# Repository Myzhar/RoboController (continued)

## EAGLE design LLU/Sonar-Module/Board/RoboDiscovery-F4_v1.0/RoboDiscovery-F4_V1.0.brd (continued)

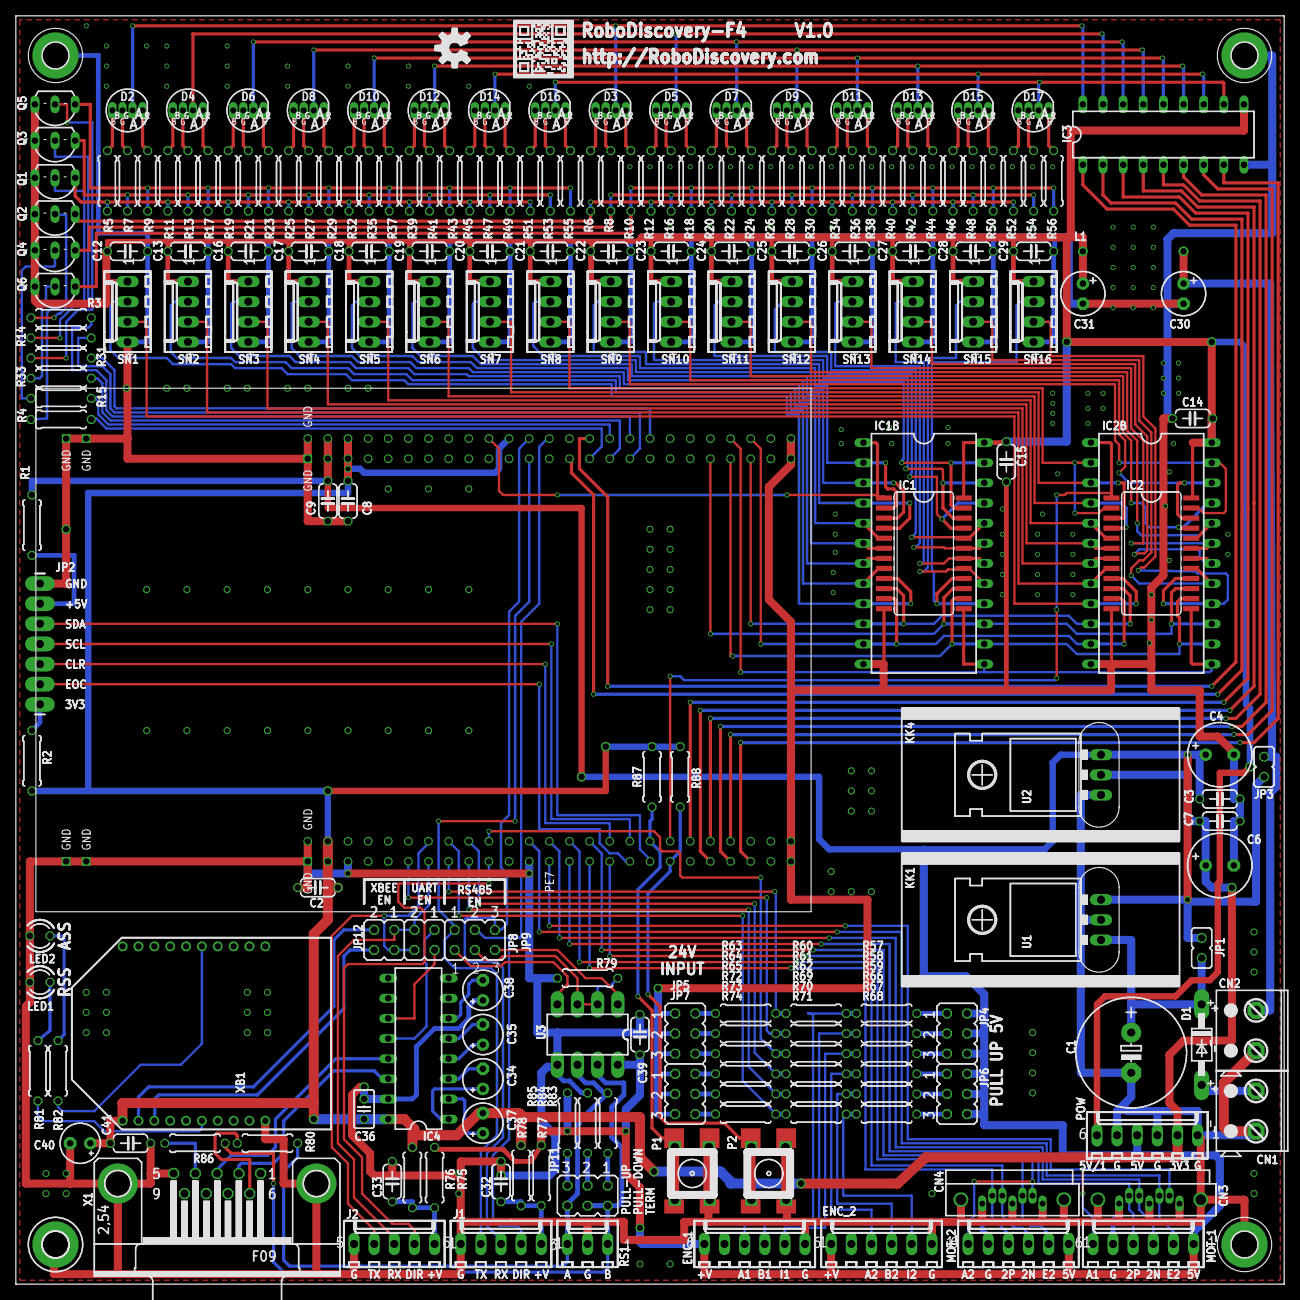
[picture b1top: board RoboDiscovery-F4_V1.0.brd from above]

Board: 2 copper layers, 160.0 x 160.0 mm, 212 parts (0 on the bottom side), 202 nets.

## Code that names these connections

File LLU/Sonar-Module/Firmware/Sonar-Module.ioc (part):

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Mcu.Name=STM32F407V(E-G)Tx
Mcu.Package=LQFP100
Mcu.UserName=STM32F407VGTx
PA0-WKUP.GPIOParameters=GPIO_Label,GPIO_PuPd,GPIO_Mode
PA0-WKUP.GPIO_Label=USER_BUT
PA0-WKUP.GPIO_Mode=GPIO_MODE_INPUT
PA0-WKUP.GPIO_PuPd=GPIO_NOPULL
PA0-WKUP.Signal=GPIO_Input
PA1.GPIOParameters=GPIO_Label,GPIO_Speed,GPIO_ModeDefaultPP,GPIO_PuPd
PA1.GPIO_Label=ENC1_B
PA1.GPIO_ModeDefaultPP=GPIO_MODE_AF_PP
PA1.GPIO_PuPd=GPIO_NOPULL
PA1.GPIO_Speed=GPIO_SPEED_LOW
PA1.Signal=S_TIM2_CH2
PA10.GPIOParameters=GPIO_Label,GPIO_Speed,GPIO_PuPd,GPIO_Mode
PA10.GPIO_Label=MUX_INH
PA10.GPIO_Mode=GPIO_MODE_OUTPUT_PP
PA10.GPIO_PuPd=GPIO_NOPULL
PA10.GPIO_Speed=GPIO_SPEED_LOW
PA10.Signal=GPIO_Output
PA11.Mode=Device_Only
PA11.Signal=USB_OTG_FS_DM
PA12.Mode=Device_Only
PA12.Signal=USB_OTG_FS_DP
PA2.GPIOParameters=GPIO_Label,GPIO_Speed,GPIO_PuPd,GPIO_Mode
PA2.GPIO_Label=F4_UART2_TX
PA2.GPIO_Mode=GPIO_MODE_AF_PP
PA2.GPIO_PuPd=GPIO_NOPULL
PA2.GPIO_Speed=GPIO_SPEED_LOW
PA2.Mode=Asynchronous
PA2.Signal=USART2_TX
PA3.GPIOParameters=GPIO_Label,GPIO_Speed,GPIO_PuPd,GPIO_Mode
PA3.GPIO_Label=F4_UART2_RX
PA3.GPIO_Mode=GPIO_MODE_AF_PP
PA3.GPIO_PuPd=GPIO_NOPULL
PA3.GPIO_Speed=GPIO_SPEED_LOW
PA3.Mode=Asynchronous
PA3.Signal=USART2_RX
PA4.GPIOParameters=GPIO_Label,GPIO_PuPd,GPIO_Mode
PA4.GPIO_Label=ENC2_IDX
PA4.GPIO_Mode=GPIO_MODE_INPUT
PA4.GPIO_PuPd=GPIO_NOPULL
PA4.Signal=GPIO_Input
PA5.GPIOParameters=GPIO_Label,GPIO_Speed,GPIO_ModeDefaultPP,GPIO_PuPd
PA5.GPIO_Label=ENC1_A
PA5.GPIO_ModeDefaultPP=GPIO_MODE_AF_PP
PA5.GPIO_PuPd=GPIO_NOPULL
PA5.GPIO_Speed=GPIO_SPEED_LOW
PA5.Signal=S_TIM2_CH1_ETR
PA6.GPIOParameters=GPIO_Label,GPIO_Speed,GPIO_ModeDefaultPP,GPIO_PuPd
PA6.GPIO_Label=ENC2_A
PA6.GPIO_ModeDefaultPP=GPIO_MODE_AF_PP
PA6.GPIO_PuPd=GPIO_NOPULL
PA6.GPIO_Speed=GPIO_SPEED_LOW
PA6.Signal=S_TIM3_CH1
PA7.GPIOParameters=GPIO_Label,GPIO_Speed,GPIO_ModeDefaultPP,GPIO_PuPd
PA7.GPIO_Label=ENC2_B
PA7.GPIO_ModeDefaultPP=GPIO_MODE_AF_PP
PA7.GPIO_PuPd=GPIO_NOPULL
PA7.GPIO_Speed=GPIO_SPEED_LOW
PA7.Signal=S_TIM3_CH2
PA8.GPIOParameters=GPIO_Label,GPIO_Speed,GPIO_PuPd,GPIO_Mode
PA8.GPIO_Label=MUX_C
PA8.GPIO_Mode=GPIO_MODE_OUTPUT_PP
PA8.GPIO_PuPd=GPIO_NOPULL
PA8.GPIO_Speed=GPIO_SPEED_LOW
PA8.Signal=GPIO_Output
PA9.GPIOParameters=GPIO_Label,GPIO_Speed,GPIO_PuPd,GPIO_Mode
PA9.GPIO_Label=MUX_D
PA9.GPIO_Mode=GPIO_MODE_OUTPUT_PP
PA9.GPIO_PuPd=GPIO_NOPULL
PA9.GPIO_Speed=GPIO_SPEED_LOW
PA9.Signal=GPIO_Output
PB10.GPIOParameters=GPIO_Label,GPIO_Speed,GPIO_PuPd,GPIO_Mode
PB10.GPIO_Label=BMP085_SCL
PB10.GPIO_Mode=GPIO_MODE_AF_OD
PB10.GPIO_PuPd=GPIO_NOPULL
PB10.GPIO_Speed=GPIO_SPEED_LOW
PB10.Mode=I2C
PB10.Signal=I2C2_SCL
PB11.GPIOParameters=GPIO_Label,GPIO_Speed,GPIO_PuPd,GPIO_Mode
PB11.GPIO_Label=BMP085_SDA
PB11.GPIO_Mode=GPIO_MODE_AF_OD
PB11.GPIO_PuPd=GPIO_NOPULL
PB11.GPIO_Speed=GPIO_SPEED_LOW
PB11.Mode=I2C
PB11.Signal=I2C2_SDA
PB12.GPIOParameters=GPIO_Label,GPIO_PuPd,GPIO_Mode
PB12.GPIO_Label=P1
PB12.GPIO_Mode=GPIO_MODE_INPUT
PB12.GPIO_PuPd=GPIO_NOPULL
PB12.Signal=GPIO_Input
PB13.GPIOParameters=GPIO_Label,GPIO_PuPd,GPIO_Mode
PB13.GPIO_Label=P2
PB13.GPIO_Mode=GPIO_MODE_INPUT
PB13.GPIO_PuPd=GPIO_NOPULL
PB13.Signal=GPIO_Input
PB14.GPIOParameters=GPIO_Label,GPIO_Speed,GPIO_ModeDefaultPP,GPIO_PuPd
PB14.GPIO_Label=ECHO_MUX
PB14.GPIO_ModeDefaultPP=GPIO_MODE_AF_PP
PB14.GPIO_PuPd=GPIO_NOPULL
PB14.GPIO_Speed=GPIO_SPEED_LOW
PB14.Signal=S_TIM12_CH1
PB2.GPIOParameters=GPIO_Label,GPIO_Speed,GPIO_PuPd,GPIO_Mode
PB2.GPIO_Label=MOTOR1_EN
PB2.GPIO_Mode=GPIO_MODE_OUTPUT_PP
PB2.GPIO_PuPd=GPIO_NOPULL
PB2.GPIO_Speed=GPIO_SPEED_LOW
PB2.Signal=GPIO_Output
PB5.GPIOParameters=GPIO_Label,GPIO_Speed,GPIO_PuPd,GPIO_Mode
PB5.GPIO_Label=F4_UART1_DIR
PB5.GPIO_Mode=GPIO_MODE_OUTPUT_PP
PB5.GPIO_PuPd=GPIO_NOPULL
PB5.GPIO_Speed=GPIO_SPEED_HIGH
PB5.Signal=GPIO_Output
PB6.GPIOParameters=GPIO_Label,GPIO_Speed,GPIO_PuPd,GPIO_Mode
PB6.GPIO_Label=F4_UART1_TX
PB6.GPIO_Mode=GPIO_MODE_AF_PP
PB6.GPIO_PuPd=GPIO_NOPULL
PB6.GPIO_Speed=GPIO_SPEED_LOW
PB6.Mode=Asynchronous
PB6.Signal=USART1_TX
PB7.GPIOParameters=GPIO_Label,GPIO_Speed,GPIO_PuPd,GPIO_Mode
PB7.GPIO_Label=F4_UART1_RX
PB7.GPIO_Mode=GPIO_MODE_AF_PP
PB7.GPIO_PuPd=GPIO_NOPULL
PB7.GPIO_Speed=GPIO_SPEED_LOW
PB7.Mode=Asynchronous
PB7.Signal=USART1_RX
PB9.GPIOParameters=GPIO_Label,GPIO_Speed,GPIO_ModeDefaultPP,GPIO_PuPd
PB9.GPIO_Label=TRIGGER_MUX
PB9.GPIO_ModeDefaultPP=GPIO_MODE_AF_PP
PB9.GPIO_PuPd=GPIO_NOPULL
PB9.GPIO_Speed=GPIO_SPEED_LOW
PB9.Signal=S_TIM11_CH1
PC4.GPIOParameters=GPIO_Label,GPIO_PuPd,GPIO_Mode
PC4.GPIO_Label=ENC1_IDX
PC4.GPIO_Mode=GPIO_MODE_INPUT
PC4.GPIO_PuPd=GPIO_NOPULL
PC4.Signal=GPIO_Input
PC5.GPIOParameters=GPIO_Label,GPIO_Speed,GPIO_PuPd,GPIO_Mode
PC5.GPIO_Label=F4_UART2_DIR
PC5.GPIO_Mode=GPIO_MODE_OUTPUT_PP
PC5.GPIO_PuPd=GPIO_NOPULL
PC5.GPIO_Speed=GPIO_SPEED_LOW
PC5.Signal=GPIO_Output
PC8.GPIOParameters=GPIO_Label,GPIO_Speed,GPIO_PuPd,GPIO_Mode
PC8.GPIO_Label=MUX_A
PC8.GPIO_Mode=GPIO_MODE_OUTPUT_PP
PC8.GPIO_PuPd=GPIO_NOPULL
PC8.GPIO_Speed=GPIO_SPEED_LOW
PC8.Signal=GPIO_Output
PC9.GPIOParameters=GPIO_Label,GPIO_Speed,GPIO_PuPd,GPIO_Mode
PC9.GPIO_Label=MUX_B
PC9.GPIO_Mode=GPIO_MODE_OUTPUT_PP
PC9.GPIO_PuPd=GPIO_NOPULL
PC9.GPIO_Speed=GPIO_SPEED_LOW
PC9.Signal=GPIO_Output
PD0.GPIOParameters=GPIO_Label,GPIO_Speed,GPIO_PuPd,GPIO_Mode
PD0.GPIO_Label=TR_S1_RED
PD0.GPIO_Mode=GPIO_MODE_OUTPUT_PP
PD0.GPIO_PuPd=GPIO_NOPULL
PD0.GPIO_Speed=GPIO_SPEED_HIGH
PD0.Signal=GPIO_Output
PD1.GPIOParameters=GPIO_Label,GPIO_Speed,GPIO_PuPd,GPIO_Mode
PD1.GPIO_Label=TR_S1_GREEN
PD1.GPIO_Mode=GPIO_MODE_OUTPUT_PP
PD1.GPIO_PuPd=GPIO_NOPULL
PD1.GPIO_Speed=GPIO_SPEED_HIGH
PD1.Signal=GPIO_Output
PD10.GPIOParameters=GPIO_Label,GPIO_Speed,GPIO_PuPd,GPIO_Mode
PD10.GPIO_Label=KLED_5
PD10.GPIO_Mode=GPIO_MODE_OUTPUT_PP
PD10.GPIO_PuPd=GPIO_NOPULL
PD10.GPIO_Speed=GPIO_SPEED_HIGH
PD10.Signal=GPIO_Output
PD11.GPIOParameters=GPIO_Label,GPIO_Speed,GPIO_PuPd,GPIO_Mode
PD11.GPIO_Label=KLED_6
PD11.GPIO_Mode=GPIO_MODE_OUTPUT_PP
PD11.GPIO_PuPd=GPIO_NOPULL
PD11.GPIO_Speed=GPIO_SPEED_HIGH
PD11.Signal=GPIO_Output
PD12.GPIOParameters=GPIO_Label,GPIO_Speed,GPIO_PuPd,GPIO_Mode
PD12.GPIO_Label=KLED_7
PD12.GPIO_Mode=GPIO_MODE_OUTPUT_PP
PD12.GPIO_PuPd=GPIO_NOPULL
PD12.GPIO_Speed=GPIO_SPEED_HIGH
PD12.Signal=GPIO_Output
PD13.GPIOParameters=GPIO_Label,GPIO_Speed,GPIO_PuPd,GPIO_Mode
PD13.GPIO_Label=KLED_8
PD13.GPIO_Mode=GPIO_MODE_OUTPUT_PP
PD13.GPIO_PuPd=GPIO_NOPULL
PD13.GPIO_Speed=GPIO_SPEED_HIGH
PD13.Signal=GPIO_Output
PD2.GPIOParameters=GPIO_Label,GPIO_Speed,GPIO_PuPd,GPIO_Mode
PD2.GPIO_Label=TR_S1_BLUE
PD2.GPIO_Mode=GPIO_MODE_OUTPUT_PP
PD2.GPIO_PuPd=GPIO_NOPULL
PD2.GPIO_Speed=GPIO_SPEED_HIGH
PD2.Signal=GPIO_Output
PD3.GPIOParameters=GPIO_Label,GPIO_Speed,GPIO_PuPd,GPIO_Mode
PD3.GPIO_Label=TR_S2_RED
PD3.GPIO_Mode=GPIO_MODE_OUTPUT_PP
PD3.GPIO_PuPd=GPIO_NOPULL
PD3.GPIO_Speed=GPIO_SPEED_HIGH
PD3.Signal=GPIO_Output
PD4.GPIOParameters=GPIO_Label,GPIO_Speed,GPIO_PuPd,GPIO_Mode
PD4.GPIO_Label=TR_S2_GREEN
PD4.GPIO_Mode=GPIO_MODE_OUTPUT_PP
PD4.GPIO_PuPd=GPIO_NOPULL
PD4.GPIO_Speed=GPIO_SPEED_HIGH
PD4.Signal=GPIO_Output
PD5.GPIOParameters=GPIO_Label,GPIO_Speed,GPIO_PuPd,GPIO_Mode
PD5.GPIO_Label=TR_S2_BLUE
PD5.GPIO_Mode=GPIO_MODE_OUTPUT_PP
PD5.GPIO_PuPd=GPIO_NOPULL
PD5.GPIO_Speed=GPIO_SPEED_HIGH
PD5.Signal=GPIO_Output
PD6.GPIOParameters=GPIO_Label,GPIO_Speed,GPIO_PuPd,GPIO_Mode
PD6.GPIO_Label=KLED_1
PD6.GPIO_Mode=GPIO_MODE_OUTPUT_PP
PD6.GPIO_PuPd=GPIO_NOPULL
PD6.GPIO_Speed=GPIO_SPEED_HIGH
PD6.Signal=GPIO_Output
PD7.GPIOParameters=GPIO_Label,GPIO_Speed,GPIO_PuPd,GPIO_Mode
PD7.GPIO_Label=KLED_2
PD7.GPIO_Mode=GPIO_MODE_OUTPUT_PP
PD7.GPIO_PuPd=GPIO_NOPULL
PD7.GPIO_Speed=GPIO_SPEED_HIGH
PD7.Signal=GPIO_Output
PD8.GPIOParameters=GPIO_Label,GPIO_Speed,GPIO_PuPd,GPIO_Mode
PD8.GPIO_Label=KLED_3
PD8.GPIO_Mode=GPIO_MODE_OUTPUT_PP
PD8.GPIO_PuPd=GPIO_NOPULL
PD8.GPIO_Speed=GPIO_SPEED_HIGH
PD8.Signal=GPIO_Output
PD9.GPIOParameters=GPIO_Label,GPIO_Speed,GPIO_PuPd,GPIO_Mode
PD9.GPIO_Label=KLED_4
PD9.GPIO_Mode=GPIO_MODE_OUTPUT_PP
PD9.GPIO_PuPd=GPIO_NOPULL
PD9.GPIO_Speed=GPIO_SPEED_HIGH
PD9.Signal=GPIO_Output
PE10.GPIOParameters=GPIO_Label,GPIO_Speed,GPIO_ModeDefaultPP,GPIO_PuPd
PE10.GPIO_Label=PWM_CH2_N
PE10.GPIO_ModeDefaultPP=GPIO_MODE_AF_PP
PE10.GPIO_PuPd=GPIO_NOPULL
PE10.GPIO_Speed=GPIO_SPEED_LOW
PE10.Mode=PWM Generation2 CH2 CH2N
PE10.Signal=TIM1_CH2N
PE11.GPIOParameters=GPIO_Label,GPIO_Speed,GPIO_ModeDefaultPP,GPIO_PuPd
PE11.GPIO_Label=PWM_CH2_P
PE11.GPIO_ModeDefaultPP=GPIO_MODE_AF_PP
PE11.GPIO_PuPd=GPIO_NOPULL
PE11.GPIO_Speed=GPIO_SPEED_LOW
PE11.Signal=S_TIM1_CH2
PE12.GPIOParameters=GPIO_Label,GPIO_Speed,GPIO_PuPd,GPIO_Mode
PE12.GPIO_Label=MOTOR2_AUX
PE12.GPIO_Mode=GPIO_MODE_OUTPUT_PP
PE12.GPIO_PuPd=GPIO_NOPULL
PE12.GPIO_Speed=GPIO_SPEED_LOW
PE12.Signal=GPIO_Output
PE13.GPIOParameters=GPIO_Label,GPIO_Speed,GPIO_PuPd,GPIO_Mode
PE13.GPIO_Label=MOTOR2_EN
PE13.GPIO_Mode=GPIO_MODE_OUTPUT_PP
PE13.GPIO_PuPd=GPIO_NOPULL
PE13.GPIO_Speed=GPIO_SPEED_LOW
PE13.Signal=GPIO_Output
PE14.GPIOParameters=GPIO_Label,GPIO_Speed,GPIO_PuPd,GPIO_Mode
PE14.GPIO_Label=BMP085_CLR
PE14.GPIO_Mode=GPIO_MODE_OUTPUT_PP
PE14.GPIO_PuPd=GPIO_NOPULL
PE14.GPIO_Speed=GPIO_SPEED_LOW
PE14.Signal=GPIO_Output

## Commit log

2013-12-28 Primo commit
    Inizializzazione
2013-12-29 Added LGPL license files
2013-12-29 * RoboController-PID_Regulator adapted to new SDK configuration
2013-12-29 * RoboControllerServer: adapted to SDK modifications + minor changes * RoboControllerSDK: minor changes
2014-01-08 Update .gitignore
    Added OS Generated files to .gitignore
2014-01-08 * Added new "SERVER" module to SDK * Updated .gitignore with "build" folder, OS generated files and MPLABX files * Minor bugs
2014-01-08 Removed Thumbs and added License
    * Removed Thumbs.db from Android folders
    * Added license file to RobotGUI
2014-01-08 Prima versione del firmware per DsPic33FJ128MC804
2014-01-09 Update .gitignore
    * modificata ignore list per MPlabX
2014-01-16 MplabX project - Missing file update
    MplabX project - Missing file update
2014-01-21 Dspic project update
    Moved file in a proper directory and corrected some functions prototypes
2014-02-08 Android keystore updated
    / correct error in RoboControllerServer.pro
    / added math.h to CQtjoypad, not compiling under linux without it
2014-02-08 Removed some debug information.
2014-02-08 removed unusefull debug information
2014-02-08 Modify Exception Handling #5
    / Solution to issue #5
2014-02-08 Returned an "pid semi-functionally" status :)
2014-02-08 GUI enhancements
    / Started speed visualization in RobotGUI
2014-02-08 PidInit function on PID/PWM mode change.
2014-02-13 Debug function for StackPointer Error
2014-02-15 Updated ignore list for Android
2014-02-15 mod_GUI modifications
    / added QRobotConfigurationDlg / renamed CQtJoypad in QJoypad / Added
    QScreentools / more other
2014-02-16 Added Robot Configuration functions
    / updated RobotGUI for Robot Configuration / implemented speed
    visualization in RobotGUI
2014-02-18 New mod_SERVER structure
    / Introduced UDP Servers
    / created mod_EXTERN module
    / moved libmodbus to mod_EXTERN module
2014-02-18 The work on RobotServer goes on
    / Started UDP integration (not working yet)
2014-02-18 RobotServer is growing
    / To implement parsing of UDP datagrams in clients
2014-02-19 Minor changes to RobotServer
2014-02-19 Added message parsing to UDP for clients
    / TODO Error handling for UDP
2014-02-21 Interrupt test
2014-02-21 Various minor fix
2014-02-23 Reviewed UDP architecture
    / UDP client must be redesigned according to Server architecture
    / Added automatic "Server finding" functionality
2014-02-23 Lots of modifications to UDP Client/Server architecture
    / Find Server is working
    / minor changes
    / Speed request take 100% of the server. Verify!
2014-02-25 Robot Motion Control functions
    / Added function to take Robot Motion exclusive control
    / Minor changes to code structure
2014-02-26 Battery handling
    / Added GUI to calibrate battery
    / Added function to request battery charge level
    / To be coded functions to calibrate battery
    / Minor changes
2014-03-19 Added "bin" folder to RobotGUI
    / Added RobotGUI signed release Android APK
    / Added RobotGUI Windows exe compiled with MinGW_32
2014-03-22 Android UDP problems corrected
    / resolved issue binding Android app to UDP Status server
    / added server test mode
    / added battery information to SDK and GUI
2014-03-23 Aperto ramo di sviluppo Katodo
2014-03-23 New configuration values for battery #11
    Add
    WORD_ROBOT_CHARGED_BATT 219
    WORD_ROBOT_DISCHARGED_BATT 220
    as robot configuration registers.
2014-03-23 Added Battery info to RobotGUI
    / Added battery info to RobotGUI
    / Added Battery calibration functions
    / Added Battery calibration GUI
2014-03-24 Modifica {} per debug
2014-03-24 Robot Speeds request and send made better
    / Added function to request speed of both motors simultaneously
    / Added function to set speed of both motors simultaneously
    / Updated RobotGUI according to new functions for speed
    / Now the server replies with speeds of the motors if a movement command
    is received. This reduces communication bandwidth
2014-03-24 Error fix retrieving speeds
    / minor code layout correction
    / other minor fixes
2014-03-26 Modification to TCP protocol
    / Modified onTcpReadyRead to add the "TCP_START_VAL" searching!
    / Fixed a bugged "mNextTcpBlockSize=0;" setting
2014-03-26 Added #define TCP_START_VAL 0xA55A
2014-03-26 Added TCP_START_VAL to sendBlockTCP
2014-03-26 Added #define UDP_START_VAL 0xAA55
2014-03-26 Added UDP_START_VAL to sendStatusBlockUDP
2014-03-26 Updated onUdpStatusReadyRead for UDP_START_VAL
2014-03-26 UDP_START_VAL in findServer
2014-03-26 UDP_START_VAL in sendBlockUDP
2014-03-26 UDP_START_VAL in onUdpStatusReadyRead
2014-03-26 Sembra
2014-03-27 GitIgnore found modified from GitEye... I don't know why... :)
2014-03-27 Qdir is wrong, QDir is right :)
2014-03-27 Changed Qdir in QDir
2014-03-27 Added OpenCV for Linux dependencies
2014-03-27 RobotGUI has got video
    / Added QGlOpenCVWidget class
    / Added Video Widget to RobotGUI
    / Started improvement of UDP and TCP protocol
    / UDP communication has problems
2014-03-29 Network communication complete
    / TCP-UDP communication to be tested on robot
    / Added RoboController board status widgets
    / Started the porting of OpenCV webcam client on Android
2014-03-29 Windows bin updated
    / Updated Windows binaries
    / Minor changes
2014-03-29 Added RoboTestUnit
    / Added Test Unit Qt5 based to test functionality regression over time
    / Moved QWebcamClient from CORE to SERVER
2014-03-30 SUPER MODIFICATION
    / Added VIDEOSTREAMING module... qwebcamserver and qwebcamclient moved
    here
    / Deleted unuseful qDebug messages
    / Added tests to Test UNIT
    / RobotGUI is fully working
    / PID has a little bug (motors run in reverse)
2014-03-31 PID Regulator -> PID Tuner
    / Updated QCustomPlot
    / Moved QCustomPlot to Extern module
    / Minor changes
2014-03-31 Bug fixes
2014-04-02 Removed horror Macro :)
    Removed som macro in pid.c
2014-04-02 Little change to deadzone in PID
2014-04-02 Removed object file
    Removed object file
2014-04-02 TEST: Pid Reset in Dead Band Zone
    TEST: Pid Reset in Dead Band Zone
2014-04-02 Update Makefile
2014-04-02 Added .gitignore specific for HLU
2014-04-02 Added .gitignore specific for LLU
2014-04-04 New image rendering method
    / Replaced QGlOpenCVWidget with QRobotGUIVied based on QGraphicsView and
    QGraphicsScene
    / Now it is possible to see camera streaming on Android devices
    / TO BE TESTED!!!
2014-04-04 / QWebcamServer more stable / Removed cv::imshow under Linux to resolve hangup
2014-04-06 Timeout handling
    / Added control timeout on server
    / Started development of new GUI method
2014-04-08 RobotGUI correction
    / Now Joypad sends correct rotation direction
2014-04-08 Joypad virtuale in overlay
2014-04-08 Overlay Virtual Joypad almost working
2014-04-09 Solved issue with virtual joypad size
2014-04-09 RobotGUI: Enabled Streaming video under Android
    / RobotGUI: Updated Android APK
2014-04-10 Overlay Joypad ok
2014-04-10 Solved a few issue wit webcam server
2014-04-10 Webcam index changed to -1
2014-04-12 Correction to forward versus of Overlay Joypad
2014-04-24 Added Sonar Module
2014-04-29 Sonar Module handles 4 sonar sensors
2014-04-29 Separated RoboControllerServer by Webcam Server
2014-04-30 Added USB and UART to Sonar Module
2014-05-20 Sonar Folder reorganization
2014-05-29 First release of project
    Semi-Final version of Eagle file
2014-05-30 Sonar Module. Final Details
2014-05-31 RoboDiscovery-F4 V1.0 files
2014-05-31 Migration to OpenCV 2.4.9 and Qt5.3
2014-06-01 Updated readme.md for LLU
2014-06-01 RoboDiscovery - generated first base firmware
2014-06-16 Webcam server changed
    / Now webcam server transmit in multicast
    / Webcam clients can join multicast to receive streaming
    / Minor changes
2014-06-22 Modifications to UDP Server
    First modification to migrate to Multicast UDP for RobotServer
2014-06-24 HLU: added multicast server for telemetry
    / TO BE COMPLETED AND TESTED
2014-06-24 Moved Sonar Module to its own project
    / Sonar module is now under RoboDiscovery-F4 project
2014-06-24 Minor changes
2014-07-01 UDP Status Socket modified
    / Removed direct Telemetry requests
2014-07-05 Minor changes to Robot Servers
2014-07-06 HLU moved Control Server to its own thread
    / Added QRobotCtrlServer class
2014-07-12 Server structure evolved
    / Telemetry server has its own server
    / RoboController board has its own interface in a class outside
    QRobotServer
    / minor changes
2014-07-23 RoboControllerSDK/RobotGUI - Telemetry receiving
    TO BE TESTED!!!
2014-07-24 RobotGUI - Updated GUI with telemetry values
    / Added speed info
    / Added Battery info
2014-07-24 Added RobotWebcamClient-Test
2014-07-24 RobotWebcamClient-Test to be corrected
2014-07-24 RobotWebcamClient-Test & RobotWebcamServer WORKING
    / Commented QApplication::processEvents in every readyRead function to
    correct receiveing problems
2014-07-26 SDK - Added simulation mode to RoboControllerInterface
2014-07-28 SDK/Server/GUI - Many bug correction!!!
2014-07-28 Servers/GUI/SDK almost ready
    / TODO Verify why telemetry is not received by clients
2014-07-28 TELEMETRY bug to be corrected
    / to be found who's writing to the wrong port!!!
2014-07-29 Telemetry bug corrected
    / Telemetry client now works
    / Webcam server transmits a static frame if webcam not found
2014-07-29 Webcam Server/Client almost ready
    / Webcam client lost frames when included in RobotGUI
2014-07-30 Minor changes
    /
2014-07-31 Webcam and Telemetry working!
    / Added motor stop forcing on control releasing
    / Modified Webcam client adding "UDP Parsing" in thread "Run" function
    instead of in "readyReady" signal handling
    / TODO add webcam client thread stop function
2014-07-31 QWebcamClient has got TRIPLE BUFFERING
    / Webcam client uses triple buffer to store received frames
    / Webcam server adapt the size of the fragments of the frames to MTU of
    the network using UDP error message about datagram size
    / Minor changes to GUI
2014-08-01 Minor changes to webcam client/server and GUIs
2014-08-03 RobotGUI: Bug fixes
    / Solved issue with CalibrationDlg closing
    / Solved issue with automatic virtual Joypad on WEbcam view
    / Added timer to Telemetry requesting to separate it from RobotStatus
2014-08-06 Minor change to QJoypad
    / Modified the limitation of the thumb
    / Removed OpenCV 2.4.8
2014-08-07 Bug fixes
    / Fixed bug #16
    / Fixed Socket closing to eliminate warning on debug
2014-08-11 Added support for RGB-D
    / Added Q2DMapScene
    / Added Test-AsusXTionProLive-OpenNI2
    / Support only form Windows
2014-08-11 OpenNI 2 grabber added to repository
    / minor changes to XTion test
2014-08-13 Added OpenNI2 and QRgbdServer
    / QRgbdServer sends RGB stream on multicast
    / Minor Bug fixes
2014-08-14 Added OpenCV for Android
    / Removed OpneNI2 dependencies for Android
    / TODO to find a solution to Multicast issue in android
2014-08-23 Added RGBD module to SDK
    / Added RGBD module to remove dependency from OpenNI2 when not required
2014-08-23 Fixed minor bugs for Linux Compatibility
2014-08-23 Warning fixes
2014-09-05 ROS migration / Added ROS folder and first code for migration to ROS
2014-09-06 Buf fix on PWM
2014-09-06 ROS goes on
2014-09-06 ROS: velocity command almost working
2014-09-07 ROS: MyzharBot is moving using keyboard
2014-09-07 Added missing files
2014-09-11 .travis.yml for Qt5
2014-09-13 Removed ROS and FW
2014-09-23 Bug correction to QJoypad
